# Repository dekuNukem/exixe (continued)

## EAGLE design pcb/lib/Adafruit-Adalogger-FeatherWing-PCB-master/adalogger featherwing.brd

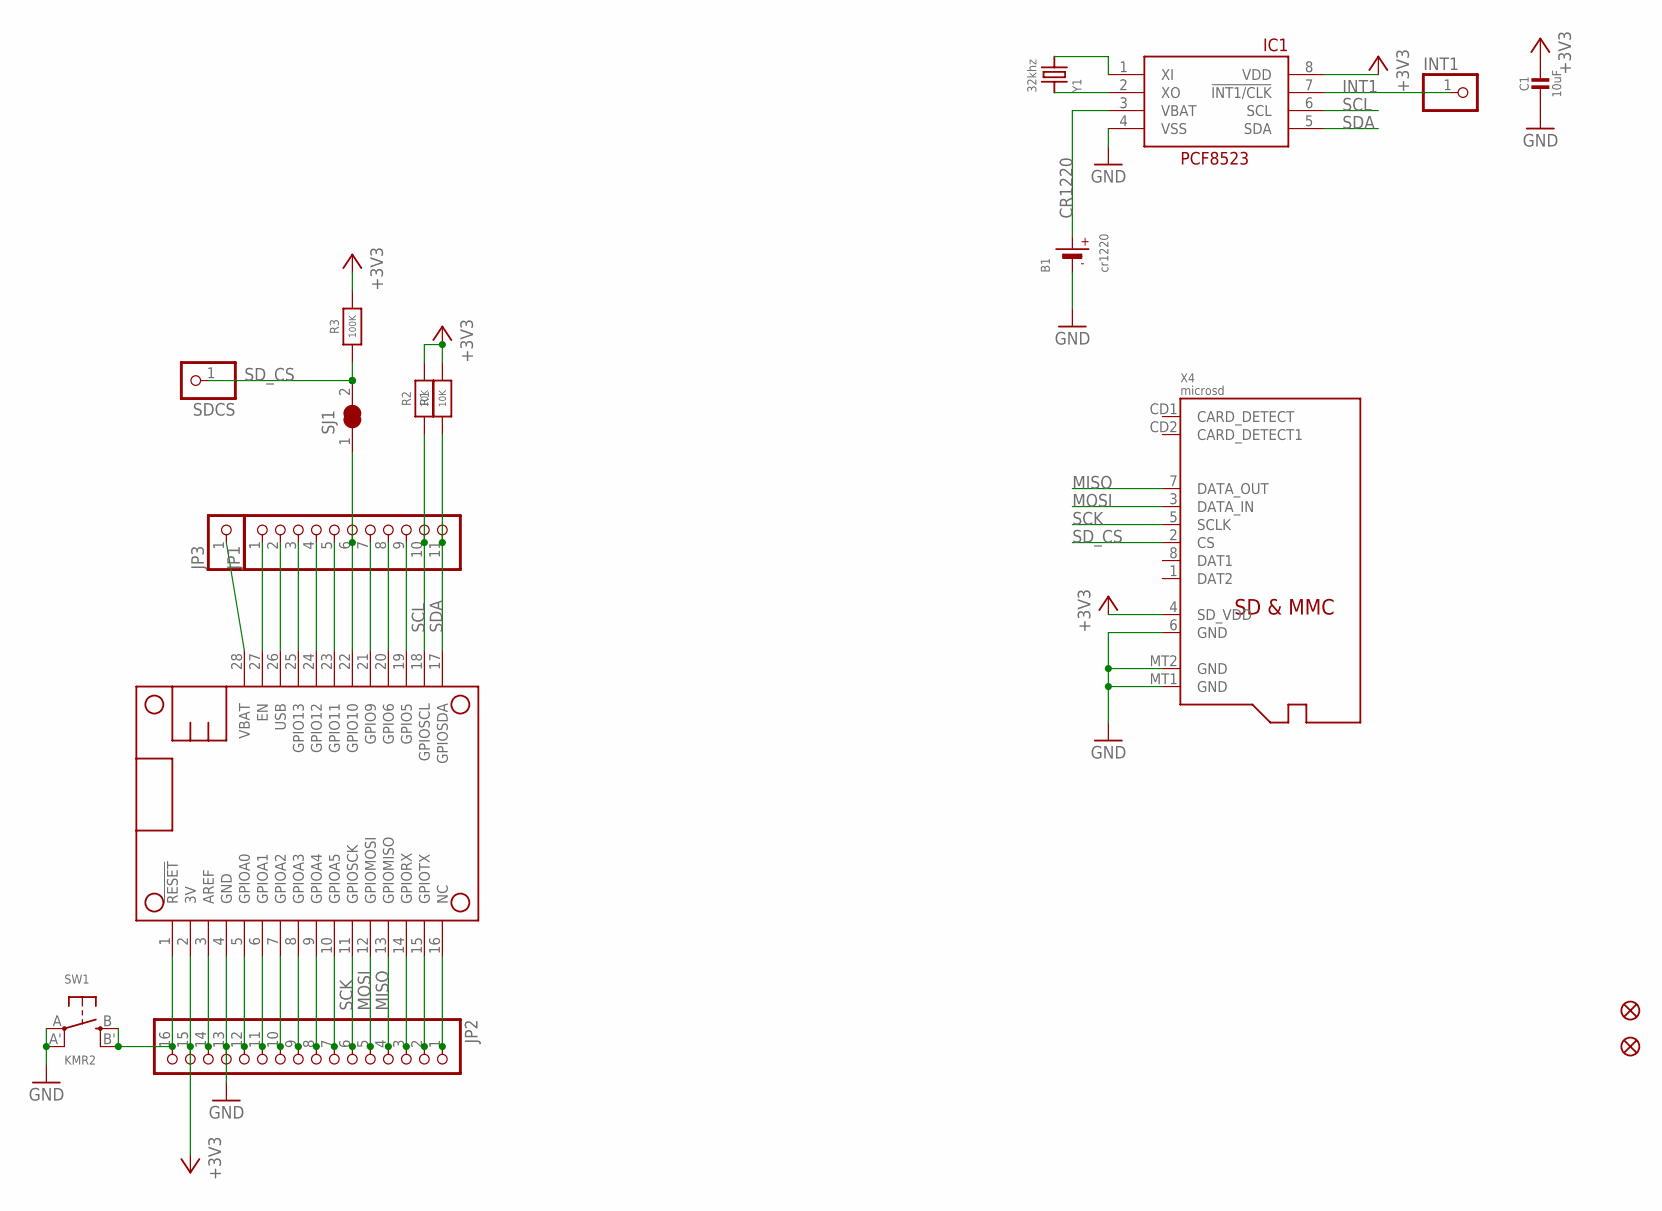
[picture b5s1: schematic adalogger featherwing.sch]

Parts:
B1: cr1220; CR1220-2
C1: 10uF; 0805-NO
FID1, FID2: FIDUCIAL""; FIDUCIAL_1MM
IC1: RTC_PCF8523T; SOIC8_150MIL
INT1: HEADER-1X1ROUND; 1X01_ROUND
JP1: HEADER-1X11; 1X11_ROUND
JP2: HEADER-1X16ROUND; 1X16_ROUND
JP3: HEADER-1X1ROUND; 1X01_ROUND
MS1: FEATHERWING_NODIM; FEATHERWING_DIM
R1, R2: 10K; 0805-NO
R3: 100K; 0805-NO
SDCS: HEADER-1X1ROUND; 1X01_ROUND
SJ1: SOLDERJUMPER_CLOSED; SOLDERJUMPER_CLOSEDWIRE
SW1: KMR2; BTN_KMR2_4.6X2.8
X4: microsd; MICROSD
Y1: 32khz; CRYSTAL_8X3.8

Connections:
+3V3: C1.1, IC1.8 (VDD), JP2.15, MS1.2 (3V), R1.2, R2.2, R3.2, X4.4 (SD_VDD)
CR1220: B1.+, IC1.3 (VBAT)
D10: JP1.6, MS1.22 (GPIO10), SJ1.1
GND: B1.-, C1.2, IC1.4 (VSS), JP2.13, MS1.4 (GND), SW1.A, SW1.A' (P1), X4.6 (GND), X4.MT1 (GND), X4.MT2 (GND)
INT1: IC1.7 (!INT1/CLK), INT1.1
MISO: JP2.4, MS1.13 (GPIOMISO), X4.7 (DATA_OUT)
MOSI: JP2.5, MS1.12 (GPIOMOSI), X4.3 (DATA_IN)
unnamed: JP2.16, MS1.1 (!RESET), SW1.B (S), SW1.B' (S1)
unnamed: JP2.1, MS1.16 (NC)
unnamed: JP1.3, MS1.25 (GPIO13)
unnamed: JP2.2, MS1.15 (GPIOTX)
unnamed: JP1.4, MS1.24 (GPIO12)
unnamed: JP2.3, MS1.14 (GPIORX)
unnamed: IC1.1 (XI), Y1.P$4 (2)
unnamed: IC1.2 (XO), Y1.P$1 (1)
unnamed: JP2.7, MS1.10 (GPIOA5)
unnamed: JP2.8, MS1.9 (GPIOA4)
unnamed: JP2.9, MS1.8 (GPIOA3)
unnamed: JP2.10, MS1.7 (GPIOA2)
unnamed: JP2.11, MS1.6 (GPIOA1)
unnamed: JP2.12, MS1.5 (GPIOA0)
unnamed: JP1.1, MS1.27 (EN)
unnamed: JP2.14, MS1.3 (AREF)
unnamed: JP1.5, MS1.23 (GPIO11)
unnamed: JP1.7, MS1.21 (GPIO9)
unnamed: JP1.8, MS1.20 (GPIO6)
unnamed: JP1.9, MS1.19 (GPIO5)
SCK: JP2.6, MS1.11 (GPIOSCK), X4.5 (SCLK)
SCL: IC1.6 (SCL), JP1.10, MS1.18 (GPIOSCL), R2.1
SDA: IC1.5 (SDA), JP1.11, MS1.17 (GPIOSDA), R1.1
SD_CS: R3.1, SDCS.1, SJ1.2, X4.2 (CS)
USB: JP1.2, MS1.26 (USB)
VBAT: JP3.1, MS1.28 (VBAT)

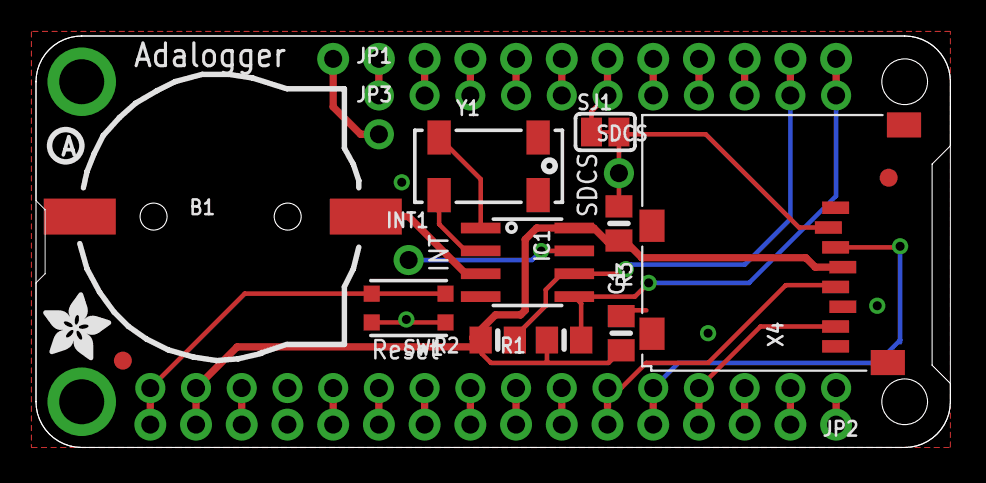
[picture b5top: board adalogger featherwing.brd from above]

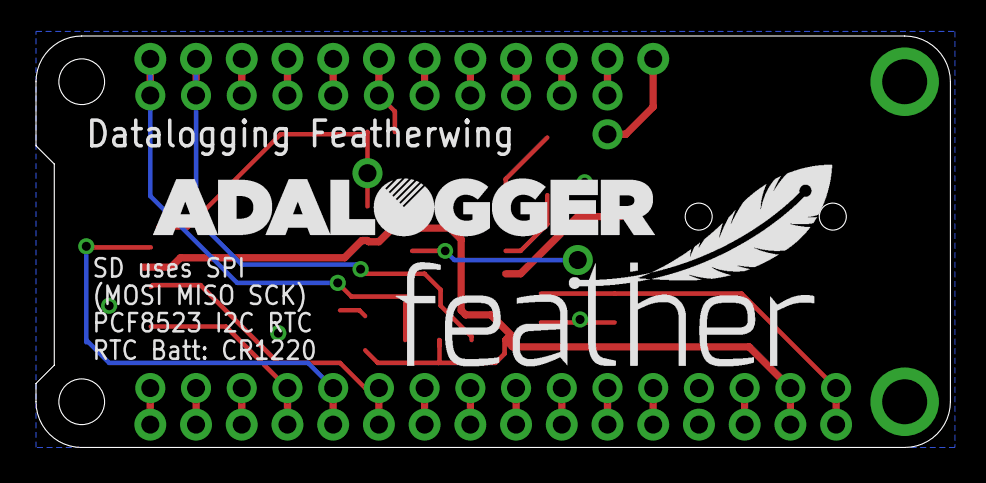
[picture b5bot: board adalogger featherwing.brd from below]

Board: 2 copper layers, 50.8 x 22.9 mm, 22 parts (2 on the bottom side), 33 nets.

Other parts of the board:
U$2: FEATHERLOGO
U$3: ADALOGGER_LOGO
U$4: ADAFRUIT_3.5MM
U$5: PCBFEAT-REV-040

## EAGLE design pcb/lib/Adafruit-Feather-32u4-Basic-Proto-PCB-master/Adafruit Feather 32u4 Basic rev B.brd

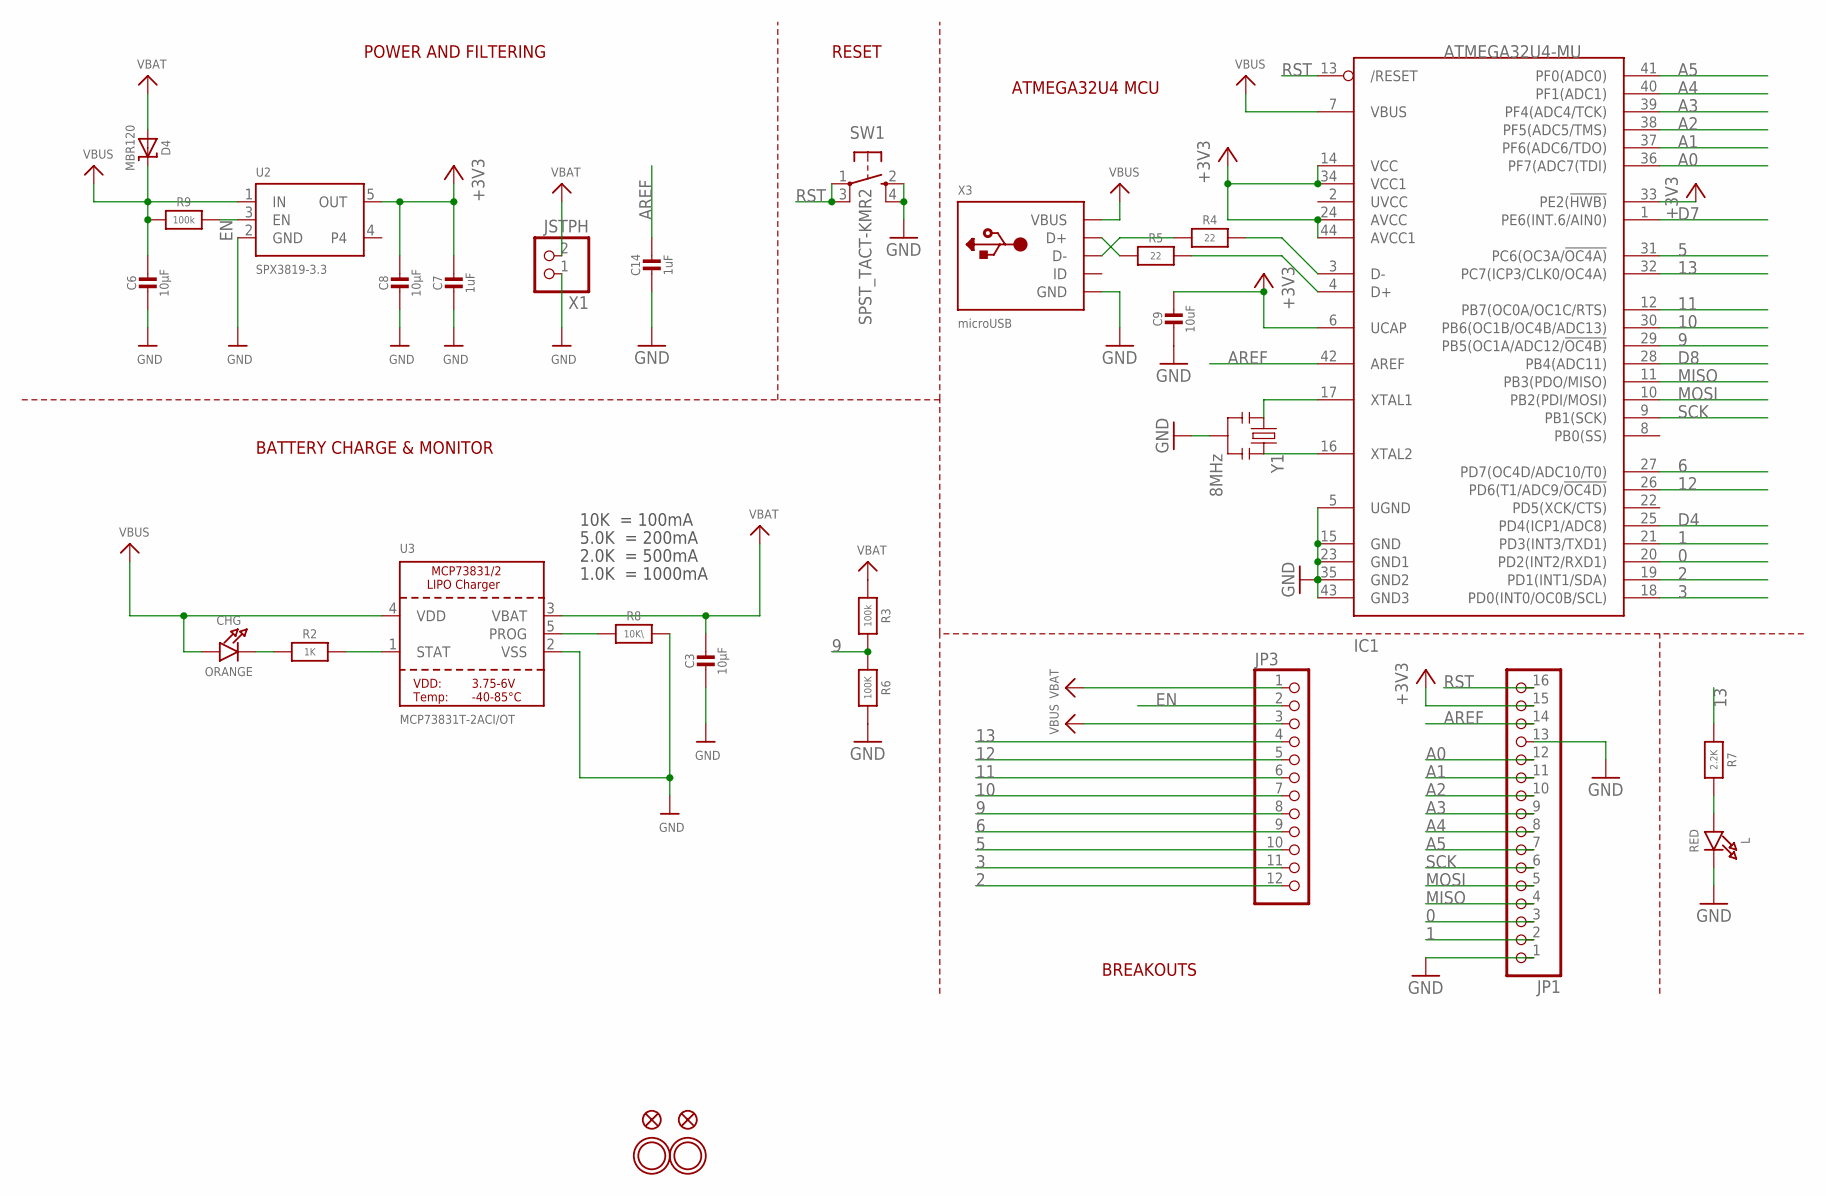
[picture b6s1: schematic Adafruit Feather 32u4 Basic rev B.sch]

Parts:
C3, C6, C8: 10µF; 0805-NO
C7, C14: 1uF; 0603-NO
C9: 10uF; 0805-NO
CHG: ORANGE; CHIPLED_0805_NOOUTLINE
D4: MBR120; SOD-123
IC1: ATMEGA32U4-MU; TQFN44_7MM
JP1: HEADER-1X16ROUND; 1X16_ROUND
JP3: HEADER-1X12; 1X12_ROUND
L: RED; CHIPLED_0805_NOOUTLINE
R2: 1K; 0603-NO
R3, R9: 100k; 0603-NO
R4, R5: 22; 0603-NO
R6: 100K; _0603MP
R7: 2.2K; 0603-NO
R8: 10K\; 0603-NO
SW1: SPST_TACT-KMR2; KMR2
U2: SPX3819-3.3; SOT23-5
U3: MCP73831T-2ACI/OT; SOT23-5
U$31, U$32: MOUNTINGHOLE2.5; MOUNTINGHOLE_2.5_PLATED
U$34, U$35: FIDUCIAL""; FIDUCIAL_1MM
X1: JSTPH; JSTPH2
X3: microUSB; 4UCONN_20329_V2
Y1: 8MHz; RESONATOR-SMD

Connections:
0: IC1.20 (PD2(INT2/RXD1)), JP1.3
1: IC1.21 (PD3(INT3/TXD1)), JP1.2
2: IC1.19 (PD1(INT1/SDA)), JP3.12
3: IC1.18 (PD0(INT0/OC0B/SCL)), JP3.11
5: IC1.31 (PC6(OC3A/!OC4A)), JP3.10
6: IC1.27 (PD7(OC4D/ADC10/T0)), JP3.9
9: IC1.29 (PB5(OC1A/ADC12/!OC4B)), JP3.8, R3.2, R6.1
10: IC1.30 (PB6(OC1B/OC4B/ADC13)), JP3.7
11: IC1.12 (PB7(OC0A/OC1C/RTS)), JP3.6
12: IC1.26 (PD6(T1/ADC9/!OC4D)), JP3.5
13: IC1.32 (PC7(ICP3/CLK0/OC4A)), JP3.4, R7.1
+3V3: C7.1, C8.1, C9.1, IC1.6 (UCAP), IC1.14 (VCC), IC1.24 (AVCC), IC1.33 (PE2(!HWB)), IC1.34 (VCC1), IC1.44 (AVCC1), JP1.15, U2.5 (OUT)
A0: IC1.36 (PF7(ADC7(TDI)), JP1.12
A1: IC1.37 (PF6(ADC6/TDO)), JP1.11
A2: IC1.38 (PF5(ADC5/TMS)), JP1.10
A3: IC1.39 (PF4(ADC4/TCK)), JP1.9
A4: IC1.40 (PF1(ADC1)), JP1.8
A5: IC1.41 (PF0(ADC0)), JP1.7
AREF: C14.1, IC1.42 (AREF), JP1.14
D4: IC1.25 (PD4(ICP1/ADC8))
D7: IC1.1 (PE6(INT.6/AIN0))
D8: IC1.28 (PB4(ADC11))
D+: IC1.4 (D+), R5.2
D-: IC1.3 (D-), R4.2
EN: JP3.2, R9.2, U2.3 (EN)
GND: C3.2, C6.2, C7.2, C8.2, C9.2, C14.2, IC1.5 (UGND), IC1.15 (GND), IC1.23 (GND1), IC1.35 (GND2), IC1.43 (GND3), JP1.1, JP1.13, L.C, R6.2, R8.2, SW1.2 (S), SW1.4 (S1), U2.2 (GND), U3.2 (VSS), X1.1, X3.BASE@1 (GND), X3.BASE@2 (GND), X3.GND, X3.SPRT@1 (GND), X3.SPRT@2 (GND), X3.SPRT@3 (GND), X3.SPRT@4 (GND), Y1.2
MISO: IC1.11 (PB3(PDO/MISO)), JP1.4
MOSI: IC1.10 (PB2(PDI/MOSI)), JP1.5
unnamed: CHG.C, R2.1
unnamed: L.A, R7.2
unnamed: R2.2, U3.1 (STAT)
unnamed: R8.1, U3.5 (PROG)
unnamed: IC1.16 (XTAL2), Y1.3
unnamed: IC1.17 (XTAL1), Y1.1
unnamed: R5.1, X3.D+
unnamed: R4.1, X3.D-
RST: IC1.13 (/RESET), JP1.16, SW1.1, SW1.3 (P1)
SCK: IC1.9 (PB1(SCK)), JP1.6
VBAT: C3.1, D4.A, JP3.1, R3.1, U3.3 (VBAT), X1.2
VBUS: C6.1, CHG.A, D4.C, IC1.7 (VBUS), JP3.3, R9.1, U2.1 (IN), U3.4 (VDD), X3.VBUS

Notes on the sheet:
POWER AND FILTERING
RESET
ATMEGA32U4 MCU
10K = 100mA
5.0K = 200mA
2.0K = 500mA
1.0K = 1000mA
BATTERY CHARGE & MONITOR
BREAKOUTS

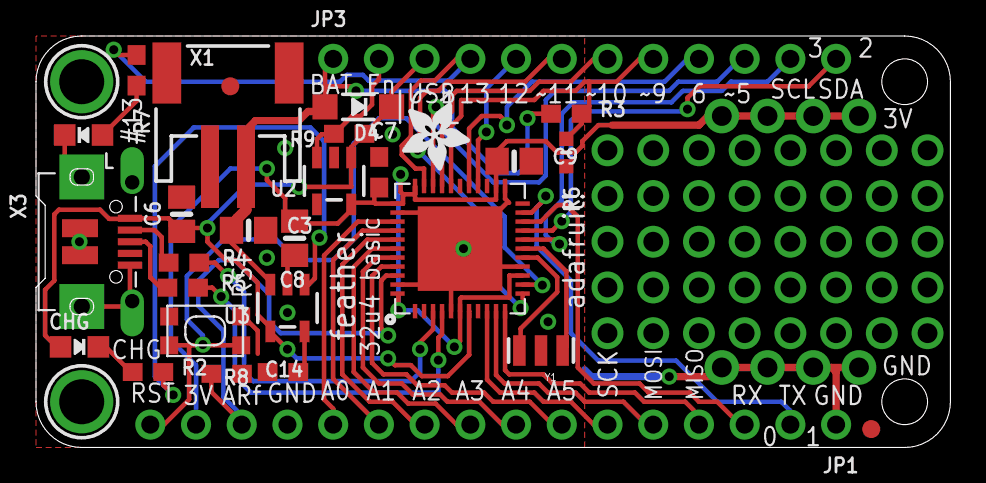
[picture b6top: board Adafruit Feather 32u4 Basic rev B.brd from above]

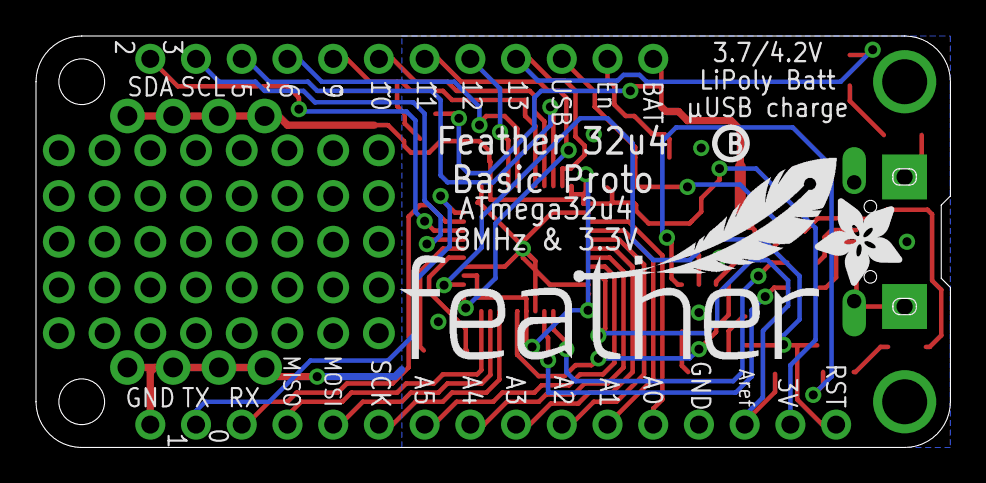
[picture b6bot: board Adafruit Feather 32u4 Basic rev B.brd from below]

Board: 2 copper layers, 50.8 x 22.9 mm, 34 parts (3 on the bottom side), 37 nets.

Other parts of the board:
U$4: ADAFRUIT_5MM
U$5: FEATHERLOGO
U$6: PCBFEAT-REV-040
U$7: ADAFRUIT_3.5MM

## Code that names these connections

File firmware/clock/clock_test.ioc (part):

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Mcu.Name=STM32F072C(8-B)Tx
Mcu.Package=LQFP48
Mcu.UserName=STM32F072C8Tx
PA0.GPIOParameters=PinState,GPIO_Label,GPIO_ModeDefaultOutputPP
PA0.GPIO_Label=SD_CS
PA0.GPIO_ModeDefaultOutputPP=GPIO_MODE_OUTPUT_PP
PA0.PinState=GPIO_PIN_SET
PA0.Signal=GPIO_Output
PA1.Mode=IN1
PA1.Signal=ADC_IN1
PA11.Mode=Device
PA11.Signal=USB_DM
PA12.Mode=Device
PA12.Signal=USB_DP
PA13.Mode=Serial_Wire
PA13.Signal=SYS_SWDIO
PA14.Mode=Serial_Wire
PA14.Signal=SYS_SWCLK
PA15.GPIOParameters=PinState,GPIO_Label,GPIO_ModeDefaultOutputPP
PA15.GPIO_Label=EXIXE_RESET
PA15.GPIO_ModeDefaultOutputPP=GPIO_MODE_OUTPUT_OD
PA15.PinState=GPIO_PIN_SET
PA15.Signal=GPIO_Output
PA6.GPIOParameters=PinState,GPIO_Label,GPIO_ModeDefaultOutputPP
PA6.GPIO_Label=OWIRE_DATA
PA6.GPIO_ModeDefaultOutputPP=GPIO_MODE_OUTPUT_OD
PA6.PinState=GPIO_PIN_SET
PA6.Signal=GPIO_Output
PA7.GPIOParameters=PinState,GPIO_Label
PA7.GPIO_Label=USER_LED
PA7.PinState=GPIO_PIN_SET
PA7.Signal=GPIO_Output
PB0.GPIOParameters=PinState,GPIO_Label
PB0.GPIO_Label=EXIXE1_CS
PB0.PinState=GPIO_PIN_SET
PB0.Signal=GPIO_Output
PB1.GPIOParameters=PinState,GPIO_Label
PB1.GPIO_Label=EXIXE2_CS
PB1.PinState=GPIO_PIN_SET
PB1.Signal=GPIO_Output
PB10.Mode=Asynchronous
PB10.Signal=USART3_TX
PB11.Mode=Asynchronous
PB11.Signal=USART3_RX
PB12.GPIOParameters=PinState,GPIO_Label
PB12.GPIO_Label=EXIXE4_CS
PB12.PinState=GPIO_PIN_SET
PB12.Signal=GPIO_Output
PB13.GPIOParameters=PinState,GPIO_Label
PB13.GPIO_Label=EXIXE5_CS
PB13.PinState=GPIO_PIN_SET
PB13.Signal=GPIO_Output
PB14.GPIOParameters=PinState,GPIO_Label
PB14.GPIO_Label=EXIXE6_CS
PB14.PinState=GPIO_PIN_SET
PB14.Signal=GPIO_Output
PB15.GPIOParameters=GPIO_Label,GPIO_ModeDefaultEXTI
PB15.GPIO_Label=GPS_TP
PB15.GPIO_ModeDefaultEXTI=GPIO_MODE_IT_RISING
PB15.Signal=GPXTI15
PB2.GPIOParameters=PinState,GPIO_Label
PB2.GPIO_Label=EXIXE3_CS
PB2.PinState=GPIO_PIN_SET
PB2.Signal=GPIO_Output
PB3.Mode=Full_Duplex_Master
PB3.Signal=SPI1_SCK
PB4.Mode=Full_Duplex_Master
PB4.Signal=SPI1_MISO
PB5.Mode=Full_Duplex_Master
PB5.Signal=SPI1_MOSI
PB6.Mode=Asynchronous
PB6.Signal=USART1_TX
PB7.Mode=Asynchronous
PB7.Signal=USART1_RX
PB8.Mode=I2C
PB8.Signal=I2C1_SCL
PB9.Mode=I2C
PB9.Signal=I2C1_SDA
PC13.GPIOParameters=PinState,GPIO_Label
PC13.GPIO_Label=GPS_RESET
PC13.PinState=GPIO_PIN_SET
PC13.Signal=GPIO_Output
PF0-OSC_IN.GPIOParameters=GPIO_PuPd,GPIO_Label
PF0-OSC_IN.GPIO_Label=UP_BUTTON
PF0-OSC_IN.GPIO_PuPd=GPIO_PULLUP
PF0-OSC_IN.Signal=GPIO_Input
PF1-OSC_OUT.GPIOParameters=GPIO_PuPd,GPIO_Label
PF1-OSC_OUT.GPIO_Label=DOWN_BUTTON
PF1-OSC_OUT.GPIO_PuPd=GPIO_PULLUP
PF1-OSC_OUT.Signal=GPIO_Input
RCC.SYSCLKFreq_VALUE=48000000
RCC.SYSCLKSource=RCC_SYSCLKSOURCE_HSI48
board=clock_test

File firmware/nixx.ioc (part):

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Mcu.Name=STM32F042K6Tx
Mcu.Package=LQFP32
Mcu.UserName=STM32F042K6Tx
PA0.Signal=S_TIM2_CH1_ETR
PA1.Signal=S_TIM2_CH2
PA10.Signal=S_TIM1_CH3
PA11.Signal=S_TIM1_CH4
PA13.Mode=Serial_Wire
PA13.Signal=SYS_SWDIO
PA14.Mode=Serial_Wire
PA14.Signal=SYS_SWCLK
PA15.Mode=NSS_Signal_Hard_Input
PA15.Signal=SPI1_NSS
PA2.Signal=S_TIM2_CH3
PA3.Signal=S_TIM2_CH4
PA4.Signal=S_TIM14_CH1
PA5.Mode=Full_Duplex_Slave
PA5.Signal=SPI1_SCK
PA6.Mode=Full_Duplex_Slave
PA6.Signal=SPI1_MISO
PA7.Mode=Full_Duplex_Slave
PA7.Signal=SPI1_MOSI
PA8.Signal=S_TIM1_CH1
PA9.Signal=S_TIM1_CH2
PB0.Signal=S_TIM3_CH3
PB1.Signal=S_TIM3_CH4
PB3.Signal=GPIO_Output
PB4.Signal=S_TIM3_CH1
PB5.Signal=S_TIM3_CH2
PB6.Mode=Asynchronous
PB6.Signal=USART1_TX
PB7.Mode=Asynchronous
PB7.Signal=USART1_RX
PB8.Signal=S_TIM16_CH1
PF0-OSC_IN.Mode=I2C
PF0-OSC_IN.Signal=I2C1_SDA
PF1-OSC_OUT.Mode=I2C
PF1-OSC_OUT.Signal=I2C1_SCL
RCC.SYSCLKFreq_VALUE=48000000
RCC.SYSCLKSource=RCC_SYSCLKSOURCE_HSI48

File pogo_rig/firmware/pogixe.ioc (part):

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Mcu.Name=STM32F030F4Px
Mcu.Package=TSSOP20
Mcu.UserName=STM32F030F4Px
PA0.GPIOParameters=GPIO_Label
PA0.GPIO_Label=LED1
PA0.Signal=GPIO_Output
PA1.GPIOParameters=GPIO_Label
PA1.GPIO_Label=EXIXE_RST
PA1.Signal=GPIO_Output
PA13.Mode=Serial_Wire
PA13.Signal=SYS_SWDIO
PA14.Mode=Serial_Wire
PA14.Signal=SYS_SWCLK
PA2.Mode=Asynchronous
PA2.Signal=USART1_TX
PA3.Mode=Asynchronous
PA3.Signal=USART1_RX
PA4.GPIOParameters=GPIO_Label
PA4.GPIO_Label=SPI1_CS
PA4.Signal=GPIO_Output
PA5.Mode=Full_Duplex_Master
PA5.Signal=SPI1_SCK
PA6.Mode=Full_Duplex_Master
PA6.Signal=SPI1_MISO
PA7.Mode=Full_Duplex_Master
PA7.Signal=SPI1_MOSI
PB1.GPIOParameters=GPIO_Label
PB1.GPIO_Label=USER_BUTTON
PB1.Signal=GPIO_Input

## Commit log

2017-04-25 fixed formatting
2017-04-26 uc selection
2017-04-26 added cube setup
2017-04-26 started sch
2017-04-26 sorted into folders
2017-04-26 working on it
2017-04-26 added datasheet
2017-04-26 pcb routing done
2017-04-26 cleanup
2017-04-26 silkscreen update
2017-04-26 rounded corners
2017-04-26 layout adjust
2017-04-27 aligned to 2.54mm grid
2017-04-27 moved 3v3 pin
2017-04-27 sch cleanup
2017-04-27 added eeprom
2017-04-27 added name, logo
2017-05-01 started spi test
2017-05-01 using NSS, SPI test
2017-05-01 added SPI speed
2017-05-02 PA12 testpoint
2017-05-05 updated text and miter
2017-05-07 started firmware
2017-05-07 eeprom working
2017-05-07 pwm working
2017-05-07 added pulldown on BOOT0
2017-05-07 SPI SLAVE WORKING
2017-05-07 all timers inited
2017-05-08 made eeprom optional, added PF silkscreen
2017-05-08 IT recv only working
2017-05-08 DMA RX working
2017-05-08 tim17 interrupt not working
2017-05-08 bitbang 200Hz PWM on left dot
2017-05-08 finished
2017-05-08 moved to linux
2017-05-08 rough layout
2017-05-09 USBC, GPS etc
2017-05-10 added bake control
2017-05-10 positioned boards
2017-05-11 added touch
2017-05-11 routing
2017-05-12 routing done
2017-05-12 test usb working
2017-05-12 test spi working
2017-05-12 started in12
2017-05-13 animation started
2017-05-14 animation working
2017-05-14 added gps header
2017-05-14 added silkscreen labels
2017-05-14 drunk
2017-05-15 sending out
2017-05-15 final
2017-05-15 something is wrong with digit mapping
2017-05-22 started assembling
2017-05-22 tsc working
2017-05-23 fixed bake
2017-05-24 made 2 exixes
2017-05-24 delayus
2017-05-24 readscratch not working
2017-05-25 1wire working
2017-05-25 1wire working temp
2017-05-25 before GPS task
2017-05-25 GPS task working
2017-05-25 digit display working
2017-05-26 4 nixies
2017-05-26 4 nixies led
2017-05-29 all 6
2017-05-29 added nogps
2017-05-31 before gps parse
2017-05-31 gps parse time working
2017-05-31 1Hz begin
2017-05-31 wtf pc13 not working
2017-05-31 6 tube time display
2017-06-01 before button
2017-06-01 buttons and display modes
2017-06-02 before 1wire different pin
2017-06-02 1wire test
2017-06-02 led animation unsatisfactory
2017-06-02 all working apart from logging
2017-06-04 light sensor adjust
2017-06-08 new routing
2017-06-09 added todo
2017-06-12 added watchdog
2017-06-22 removed bake
2017-07-17 working on exixe 12
2017-07-18 exixe12 draft finishewd
2017-07-18 added restrict
2017-07-19 clened up added credit
2017-07-26 added nixie dot current limit resistor
2017-07-26 adjusted resistor
2017-07-26 main clock board adj
2017-07-26 ready to fab
2017-07-26 gerber exported
2017-08-04 started working on exixe 12 firmware
2017-08-05 firmware folder cleanup
2017-08-05 exixe12 working
2017-08-06 updated to use timer
2017-08-07 board cleanup
2017-08-07 rev2 fab
2017-08-14 adjusted for new exixe14 board
2017-08-15 clock working
2017-09-03 finished a 12 clock
2017-09-08 added clock14
2017-09-10 adjusted values
2017-09-10 started working on proper README
2017-09-10 added pictures
2017-09-10 clean up pcb folder
2017-09-10 didnt change anything
2017-09-10 did some testing no code changes
2017-09-10 rearranged dirctory structure
2017-09-10 added placeholder readmes
2017-09-10 code cleanup
2017-09-11 added dimension
2017-10-20 recompiled
2017-10-20 moved exixe clock to its own repo
2017-10-20 still writing readme
2017-10-23 more readme
2017-10-24 mode readme
2017-11-20 updated pictures, added arduino example
2017-11-21 added more photos
2017-11-22 adjust passive values and added bom
2017-11-30 clean up temp file
2017-11-30 added video
2017-11-30 added license
2017-12-13 added more hv isolation
2017-12-15 clean up silkscreen
2017-12-18 added getting started section
2017-12-18 update readme format
2017-12-19 added more arduino examples
2017-12-19 arduino examples are ordered
2017-12-19 increased board isolation
2017-12-19 removed gerber file
2017-12-19 improve readme
2017-12-19 added example photos
2017-12-19 started working on pogo rig
2017-12-19 working on pogo rig
2017-12-19 pogo rig mcu setup
2017-12-20 refining board design for production run
2017-12-20 adjusted passive values
2017-12-21 changed testpoints to unpopulated resistors
2017-12-21 adjusted more values
2017-12-22 working on pogo board
2017-12-23 pogo rig mostly finished
2017-12-26 changed pogo pad size
2017-12-26 increased HV width
2017-12-26 added HEX firmware file, added gerber files
2017-12-26 added firmware upload instruction, moved making some into its own md file
2017-12-29 added plate
2018-01-03 working on pogo firmware
2018-01-05 changed plate
2018-02-08 clean up readme
2018-02-09 added tube buying guide
2018-02-09 fix typos
2018-02-09 more details about getting started
2018-02-09 fix typo
2018-02-10 typos
2018-02-12 added arduino library
2018-02-12 added dual tube animation
2018-02-12 added wiring diagrams
2018-02-16 added tindie purchase link
2018-02-16 refine README
2018-02-20 adjust wording and some new pics
2018-02-20 housekeeping
2018-03-04 fine tuning descriptions
2018-03-04 adjusted table size
2018-03-05 added crossfade funtion and examples
2018-03-05 start arduino library doc
2018-03-06 adding library installtion instructions
2018-03-06 added arduino lib docs, cleanup
2018-03-06 updated contact information
2018-03-24 added unsupported tube guide
2018-03-24 added a photo
2018-03-26 fixed a bug in library
2018-04-03 fixed issue 2 and 3
2018-06-10 fixed typo
2018-06-29 fixed a stupid typo on the silkscreen
2018-07-30 fixed SPI a wiring error
2018-08-08 adjusted some comments
2018-08-08 Add instructions for IN-19 tubes.
    IN-19 tubes are the same size as IN-14 tubes.
    in-19_pin_mapping.md documents how to solder IN-19 tubes to exixe-14
    modules and the mapping between IN-19 symbols and IN-14 digits.
2018-08-09 updated docs about IN-19 tubes
2018-10-27 added date mark
2018-10-29 removed DP resistor, new pogo firmware
2019-01-17 Adding Python library
    Adding references to python library
    Adding python library
    Adding python examples that match arduino's examples
2019-02-18 added power consumption info
2019-03-18 Adding CircuitPython support
    This commit includes modified versions of the provided RPi Python library and examples, tested using the Feather M4 Express
2019-04-27 added ESD note
2019-06-08 updated pogo board
2019-06-12 updated pogo rig
2019-06-14 pogo v2 working
2019-08-27 prepare for a new production run
2019-10-25 added gerber files
2020-02-23 new production, updated BOM about unused components
2020-06-04 fixed SPI diagram
2020-08-04 Fixed time import in library and delays in loops in examples.
2020-09-20 added troubleshooting section
2020-09-20 changed section name
2020-10-05 fixed a few typos
2020-11-27 new production run
2021-08-15 added tindie and user manual link
